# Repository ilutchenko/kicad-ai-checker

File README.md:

# kischk

KiCad schematic checker (early stage).

Current code implements two foundational modules:
- `project loader`: discovers root schematic and resolves hierarchical sheets.
- `schematic parser`: parses `.kicad_sch` S-expressions into an AST.
- `netlist module`: exports/parses KiCad netlist (`kicadsexpr`) from the root schematic.
- `electrical builder`: converts AST into compact LLM-ready electrical model (components/pins/nets).

## Module: Project Loader

Path: `src/kischk/kicad/project.py`

### Purpose
Build a deterministic list of schematic files that belong to a project, starting from a project root directory.

### Main API
- `load_project(project_root: str | Path) -> LoadedProject`

### Input
- `project_root`: filesystem path to KiCad project directory.

### Output
`LoadedProject` dataclass:
- `project_root: Path`
- `project_file: Path | None`
- `root_schematic: Path`
- `schematic_files: tuple[Path, ...]`
- `hierarchy: dict[Path, tuple[Path, ...]]` where key is parent schematic and value is child sheet schematic files.

### How it works
1. Validate `project_root` exists and is a directory.
2. Select `.kicad_pro` file:
- if exactly one exists, use it
- if multiple exist, try `<dir_name>.kicad_pro`
- otherwise raise `ProjectLoaderError`
3. Select root `.kicad_sch`:
- if project file exists, expect same basename (`<project>.kicad_sch`)
- if no project file, infer from available `.kicad_sch` files (single file or `<dir_name>.kicad_sch`)
4. Recursively scan each schematic for hierarchical sheet references:
- locate `(sheet ...)` blocks
- read `(property "Sheetfile" "...")`
- resolve child path relative to parent schematic directory
5. Validate each referenced child exists.
6. Detect cyclic sheet hierarchy and raise `ProjectLoaderError`.

### Error model
Raises `ProjectLoaderError` for:
- missing/invalid project root
- ambiguous or missing root project/schematic
- missing referenced child sheet files
- cyclic hierarchy
- malformed sheet block parentheses

## Module: Schematic Parser (AST)

Path: `src/kischk/kicad/sch_parser.py` and `src/kischk/kicad/sch_model.py`

### Purpose
Parse KiCad S-expression text into a typed AST for further analysis (connectivity, semantic checks, reporting).

### Main API
- `parse_schematic_file(path: str | Path) -> ParsedSchematic`
- `parse_loaded_project(loaded: LoadedProject) -> ParsedProject`
- `parse_project(project_root: str | Path) -> ParsedProject` (loader + parser shortcut)
- `parse_sexpr(text: str, source: Path | None = None) -> SExprList`

### Input
- Single schematic file path (`parse_schematic_file`), or
- `LoadedProject` object from loader (`parse_loaded_project`), or
- project root path (`parse_project`).

### Output
AST dataclasses from `sch_model.py`:
- `SExprAtom(value: str, quoted: bool)`
- `SExprList(items: tuple[SExprNode, ...])`
- `ParsedSchematic(path: Path, root: SExprList)`
- `ParsedProject(schematics: tuple[ParsedSchematic, ...])`

### Parser behavior
- Supports nested lists, symbols, quoted strings, comments (`; ...`), and whitespace.
- Preserves string-vs-symbol distinction via `quoted` flag on atoms.
- Validates schematic top-level node starts with `kicad_sch`.
- Produces precise parse errors with `file:line:column`.

### Error model
Raises `SchematicParseError` for:
- invalid S-expression syntax (unexpected EOF, trailing content, unterminated string, etc.)
- invalid root node (not `kicad_sch`)

## End-to-end data flow

1. `load_project(project_root)` discovers all related schematic files.
2. `parse_loaded_project(loaded)` parses each file into AST.
3. `build_electrical_project(project_root)` exports/parses KiCad netlist and converts AST to compact electrical model.
4. Resulting `ElectricalProject` becomes input for future phases:
- typed schematic model extraction
- connectivity graph construction
- LLM-assisted checks
- report generation

## Module: Electrical Builder (Compact Model)

Path: `src/kischk/kicad/electrical_builder.py` and `src/kischk/kicad/electrical_model.py`

### Purpose
Reduce verbose KiCad AST into electrical information needed for rule checks and LLM prompts.

### Main API
- `build_electrical_project(project_root: str | Path) -> ElectricalProject`
- `build_electrical_from_parsed(loaded: LoadedProject, parsed: ParsedProject, netlist: NetlistData | None = None) -> ElectricalProject`

### Input
- `LoadedProject` + `ParsedProject`, optionally `NetlistData`.
- In `build_electrical_project`, netlist is auto-loaded:
- prefer `<root_schematic_basename>.net` if present
- otherwise export via `kicad-cli sch export netlist --format kicadsexpr`

### Output
`ElectricalProject` dataclass:
- `schematics: tuple[ElectricalSchematic, ...]`
- `nets: tuple[ElectricalNet, ...]`

`ElectricalSchematic`:
- `path`
- `sheet_path` (hierarchical path like `/Root/STM32`)
- `components`

`ElectricalComponent`:
- `reference`, `value`, `lib_id`, `unit`, `uuid`
- `footprint`, `datasheet`, `description`, `lcsc`, `custom_fields` (non-standard user fields only)
- `pins`

`ElectricalPin`:
- `pin_number`, `pin_name`, `direction`
- `is_no_connect`
- `net_id`, `net_name`

`ElectricalNet`:
- `net_id` from KiCad netlist `code` when netlist is available, otherwise geometry fallback (`N0001`, ...)
- optional `net_name`
- `members` (`reference`, `pin_number`)
- attached `labels`
- `is_global`

### Extraction logic
1. Parse library pin definitions from `lib_symbols` to get pin names/directions/relative coordinates.
2. Parse symbol instances (`symbol`) to build components and pin instances.
3. If netlist is available, assign pin `net_id/net_name` from netlist `(net code/name)` by `(ref, pin)`.
4. If netlist provides `pintype`, use it as pin direction in output.
5. If netlist is unavailable, fallback to geometry connectivity (`wire`, `junction`, labels, hierarchy links).

### Error model
Raises `ElectricalBuildError` for internal model consistency problems (for example, missing parsed schematics or unsupported rotations). Netlist export/parse failures are non-fatal in `build_electrical_project` and trigger geometry fallback.

## Module: Netlist

Path: `src/kischk/kicad/netlist.py`

### Purpose
Get reliable net connectivity from KiCad-generated netlist instead of inferring all nets from graphics primitives.

### Main API
- `export_netlist(schematic_file, output_file, fmt=\"kicadsexpr\") -> Path`
- `load_or_export_project_netlist(project_root) -> NetlistData`
- `parse_netlist_file(path) -> NetlistData`

### Output
- `NetlistData(nets=...)`
- `NetlistNet(code, name, net_class, nodes=...)`
- `NetlistNode(ref, pin, pintype, pinfunction)`

## Minimal usage example

```python
from kischk.kicad.project import load_project
from kischk.kicad.sch_parser import parse_loaded_project

loaded = load_project("test_kicad_project")
parsed = parse_loaded_project(loaded)

print(loaded.root_schematic)
print(len(loaded.schematic_files))
print(parsed.schematics[0].root.items[0])  # SExprAtom("kicad_sch", quoted=False)
```

## Current tests

- `tests/test_project_loader.py`
- `tests/test_sch_parser.py`
- `tests/test_netlist.py`
- `tests/test_electrical_builder.py`

Run:

```bash
PYTHONPATH=src python3 -m unittest discover -s tests -v
```

## Evaluation CLI loop

Run evaluation:

```bash
PYTHONPATH=src python3 -m kischk.cli.evaluation test_kicad_project
```

Behavior:
- runs one evaluation iteration, then asks `Run evaluation one more time? [y/N]:`
- `y`/`yes` starts another iteration and creates a new run directory
- default answer is `N` (stop)
- in non-interactive mode (no TTY stdin), it stops after one iteration automatically

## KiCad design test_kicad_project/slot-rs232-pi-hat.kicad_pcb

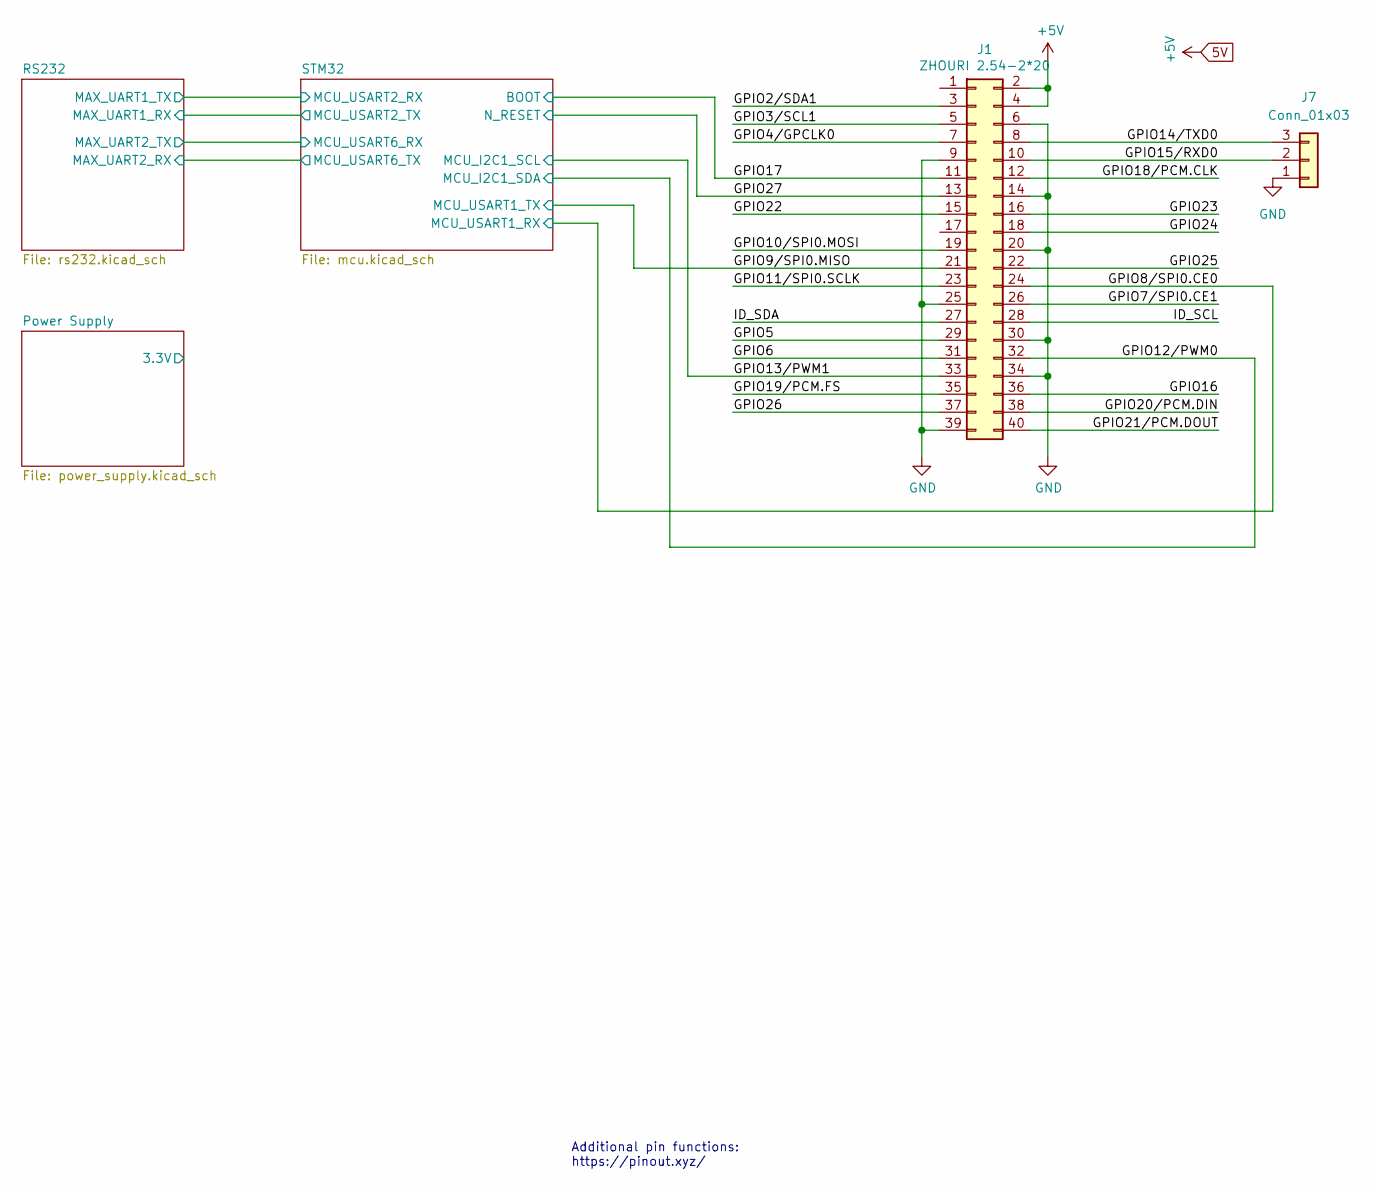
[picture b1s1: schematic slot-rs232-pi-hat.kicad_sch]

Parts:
J1: ZHOURI 2.54-2*20; PinSocket_2x20_P2.54mm_Vertical; LCSC C2977589
J7: Conn_01x03; PinSocket_1x03_P2.54mm_Vertical

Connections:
5V: J1.2, J1.4; also elsewhere on the board
/GPIO2/SDA1: J1.3
/GPIO3/SCL1: J1.5
/GPIO4/GPCLK0: J1.7
/GPIO5: J1.29
/GPIO6: J1.31
/GPIO7/SPI0.CE1: J1.26
/GPIO8/SPI0.CE0: J1.24; also elsewhere on the board
/GPIO9/SPI0.MISO: J1.21; also elsewhere on the board
/GPIO10/SPI0.MOSI: J1.19
/GPIO11/SPI0.SCLK: J1.23
/GPIO12/PWM0: J1.32; also elsewhere on the board
/GPIO13/PWM1: J1.33; also elsewhere on the board
/GPIO14/TXD0: J1.8, J7.3
/GPIO15/RXD0: J1.10, J7.2
/GPIO16: J1.36
/GPIO17: J1.11; also elsewhere on the board
/GPIO18/PCM.CLK: J1.12
/GPIO19/PCM.FS: J1.35
/GPIO20/PCM.DIN: J1.38
/GPIO21/PCM.DOUT: J1.40
/GPIO22: J1.15
/GPIO23: J1.16
/GPIO24: J1.18
/GPIO25: J1.22
/GPIO26: J1.37
/GPIO27: J1.13; also elsewhere on the board
/ID_SCL: J1.28
/ID_SDA: J1.27
GND: J1.6, J1.9, J1.14, J1.20, J1.25, J1.30, J1.34, J1.39, J7.1; also elsewhere on the board

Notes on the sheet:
Additional pin functions: https://pinout.xyz/

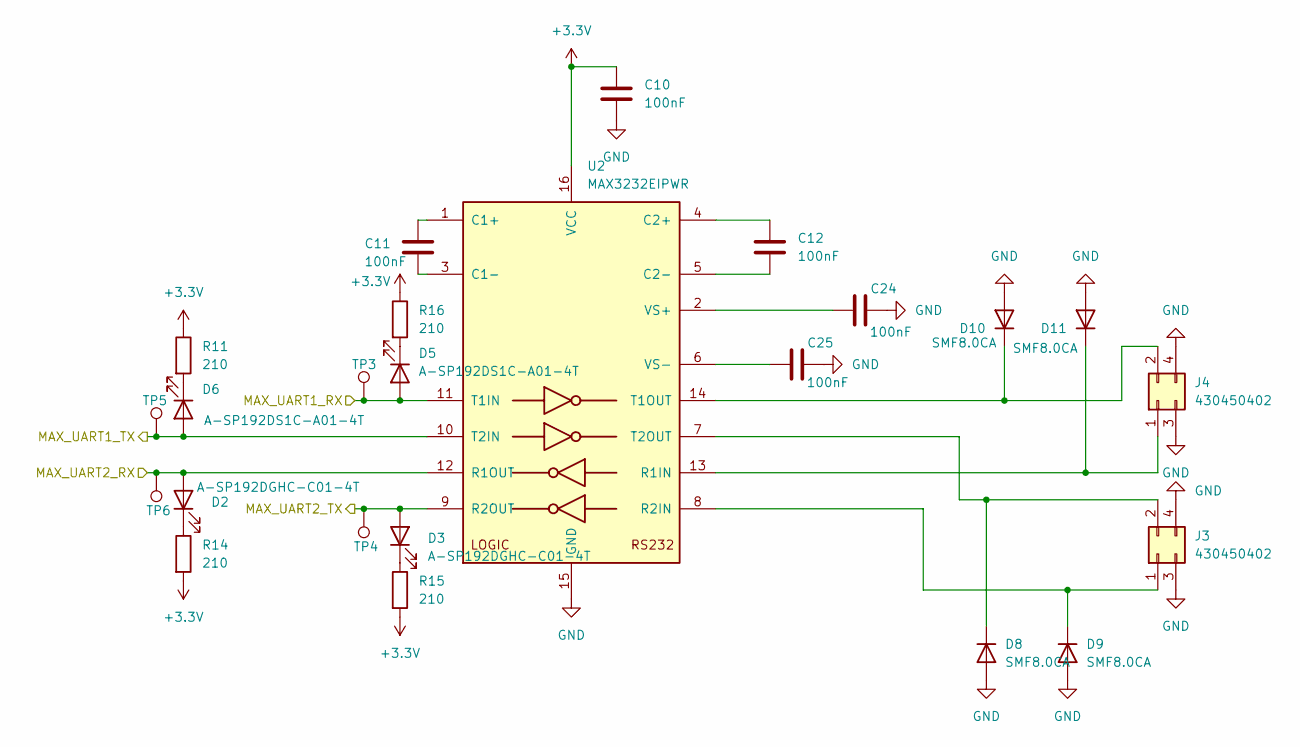
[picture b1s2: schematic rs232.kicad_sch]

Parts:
C10, C11, C12, C24, C25: 100nF; C_0603_1608Metric; LCSC C1590
D2, D3: A-SP192DGHC-C01-4T; LED_0603_1608Metric; LCSC C2286
D5, D6: A-SP192DS1C-A01-4T; LED_0603_1608Metric; LCSC C2286
D8, D9, D10, D11: SMF8.0CA; D_SOD-123F
J3, J4: 430450402; CONN_SD-43045-001_04_MOL; LCSC C587568
R11, R14, R15, R16: 210; R_0603_1608Metric; LCSC C15401
TP3, TP4, TP5, TP6: TestPoint; TestPoint_Pad_D1.5mm
U2: MAX3232EIPWR; TSSOP-16_4.4x5mm_P0.65mm

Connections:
+3.3V: C10.1, R11.1, R14.2, R15.2, R16.1, U2.16 (VCC); also elsewhere on the board
/RS232/MAX_UART1_RX: D5.2 (A), TP3.1, U2.11 (T1IN); also elsewhere on the board
/RS232/MAX_UART1_TX: D6.2 (A), TP5.1, U2.10 (T2IN); also elsewhere on the board
/RS232/MAX_UART2_RX: D2.2 (A), TP6.1, U2.12 (R1OUT); also elsewhere on the board
/RS232/MAX_UART2_TX: D3.2 (A), TP4.1, U2.9 (R2OUT); also elsewhere on the board
GND: C10.2, C24.2, C25.2, D8.2 (A), D9.2 (A), D10.2 (A), D11.2 (A), J3.3, J3.4, J4.3, J4.4, U2.15 (GND); also elsewhere on the board
unnamed: D2.1 (K), R14.1
unnamed: D3.1 (K), R15.1
unnamed: D5.1 (K), R16.2
unnamed: D6.1 (K), R11.2
unnamed: D8.1 (K), J3.2, U2.7 (T2OUT)
unnamed: D9.1 (K), J3.1, U2.8 (R2IN)
unnamed: D10.1 (K), J4.2, U2.14 (T1OUT)
unnamed: D11.1 (K), J4.1, U2.13 (R1IN)
unnamed: C11.1, U2.1 (C1+)
unnamed: C11.2, U2.3 (C1-)
unnamed: C12.1, U2.4 (C2+)
unnamed: C12.2, U2.5 (C2-)
unnamed: C24.1, U2.2 (VS+)
unnamed: C25.1, U2.6 (VS-)

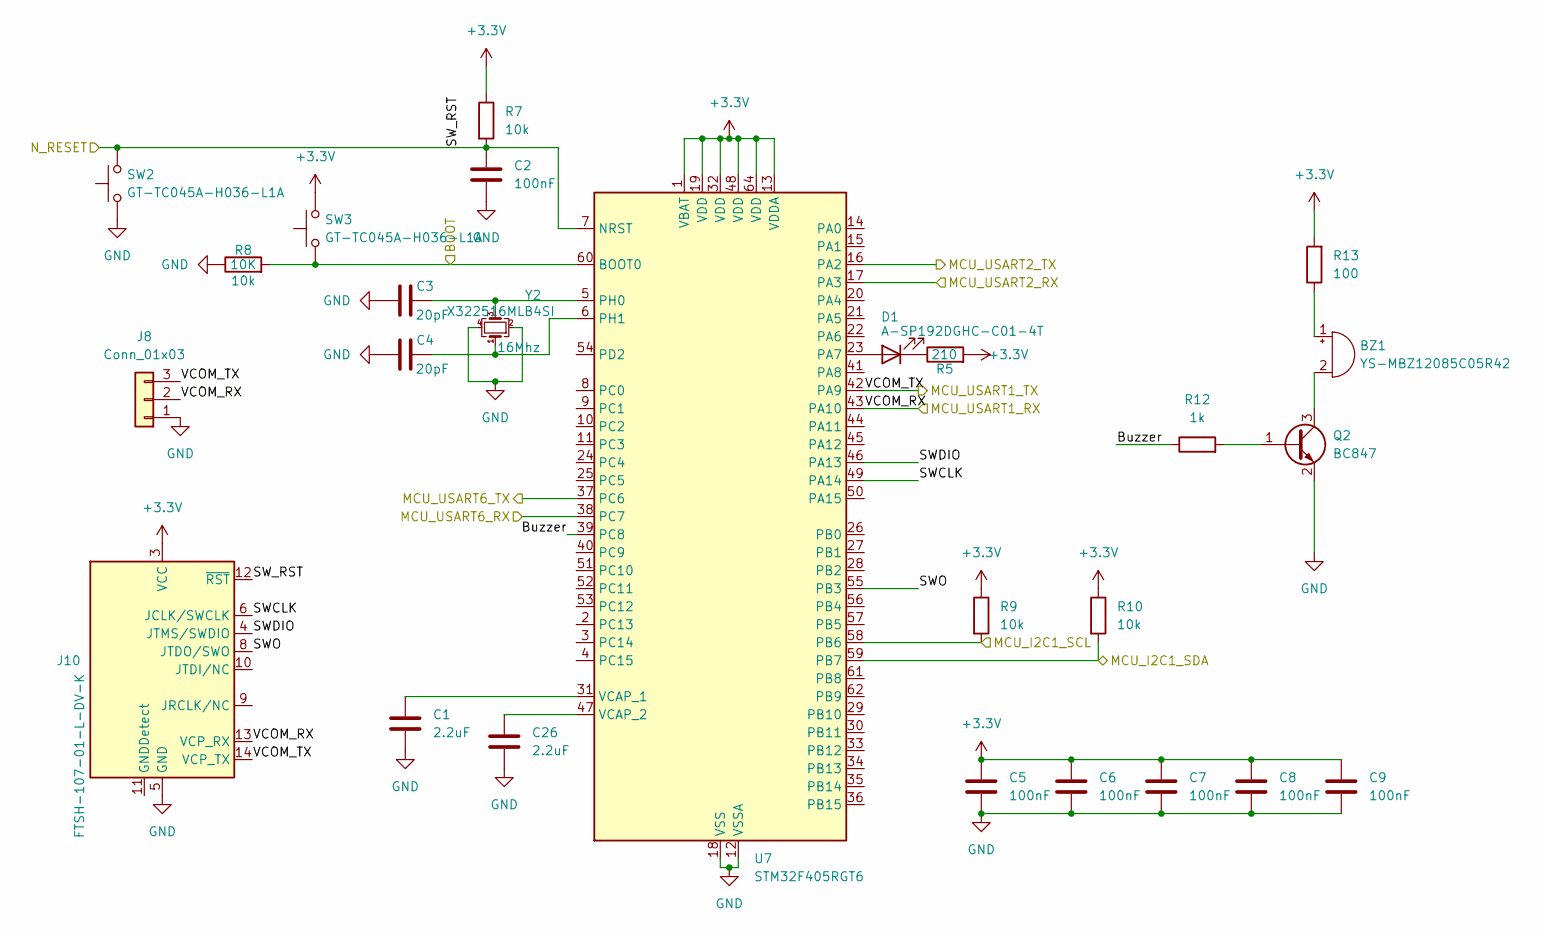
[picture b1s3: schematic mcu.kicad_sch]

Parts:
BZ1: YS-MBZ12085C05R42; Buzzer_TDK_PS1240P02BT_D12.2mm_H6.5mm; LCSC C96256
C1, C26: 2.2uF; C_0603_1608Metric; LCSC C57895
C2, C5, C6, C7, C8, C9: 100nF; C_0603_1608Metric; LCSC C1590
C3, C4: 20pF; C_0603_1608Metric; LCSC C1648
D1: A-SP192DGHC-C01-4T; LED_0603_1608Metric; LCSC C2286
J8: Conn_01x03; PinSocket_1x03_P2.54mm_Vertical
J10: FTSH-107-01-L-DV-K; PinHeader_2x07_P1.27mm_Vertical_SMD
Q2: BC847; SOT-23
R5: 210; R_0603_1608Metric; LCSC C15401
R7, R8, R9, R10: 10k; R_0603_1608Metric; LCSC C15401
R12: 1k; R_0603_1608Metric; LCSC C15401
R13: 100; R_0603_1608Metric; LCSC C15401
SW2, SW3: GT-TC045A-H036-L1A; SW_SPST_EVQP7C
U7: STM32F405RGT6; LQFP-64_10x10mm_P0.5mm
Y2: X322516MLB4SI; Crystal_SMD_3225-4Pin_3.2x2.5mm

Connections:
+3.3V: C5.1, C6.1, C7.1, C8.1, C9.1, J10.3 (VCC), R5.2, R7.1, R9.1, R10.1, R13.2, SW3.2, U7.1 (VBAT), U7.13 (VDDA), U7.19 (VDD), U7.32 (VDD), U7.48 (VDD), U7.64 (VDD); also elsewhere on the board
/GPIO8/SPI0.CE0: J8.2, J10.13 (VCP_RX), U7.43 (PA10); also elsewhere on the board
/GPIO9/SPI0.MISO: J8.3, J10.14 (VCP_TX), U7.42 (PA9); also elsewhere on the board
/GPIO12/PWM0: R10.2, U7.59 (PB7); also elsewhere on the board
/GPIO13/PWM1: R9.2, U7.58 (PB6); also elsewhere on the board
/GPIO17: R8.2, SW3.1, U7.60 (BOOT0); also elsewhere on the board
/GPIO27: C2.1, J10.12 (~RST), R7.2, SW2.2, U7.7 (NRST); also elsewhere on the board
/RS232/MAX_UART1_RX: U7.16 (PA2); also elsewhere on the board
/RS232/MAX_UART1_TX: U7.17 (PA3); also elsewhere on the board
/RS232/MAX_UART2_RX: U7.37 (PC6); also elsewhere on the board
/RS232/MAX_UART2_TX: U7.38 (PC7); also elsewhere on the board
/STM32/Buzzer: R12.1, U7.39 (PC8)
/STM32/SWCLK: J10.6 (JCLK/SWCLK), U7.49 (PA14)
/STM32/SWDIO: J10.4 (JTMS/SWDIO), U7.46 (PA13)
/STM32/SWO: J10.8 (JTDO/SWO), U7.55 (PB3)
GND: C1.2, C2.2, C3.1, C4.1, C5.2, C6.2, C7.2, C8.2, C9.2, C26.2, J8.1, J10.5 (GND), J10.7 (GND), Q2.2 (E), R8.1, SW2.1, U7.12 (VSSA), U7.18 (VSS), U7.63 (VSS), Y2.2, Y2.4; also elsewhere on the board
unnamed 39: BZ1.2 (-), Q2.3 (C); also elsewhere on the board
unnamed 40: BZ1.1 (+), R13.1; also elsewhere on the board
unnamed: D1.2 (A), U7.23 (PA7)
unnamed: D1.1 (K), R5.1
unnamed: Q2.1 (B), R12.2
unnamed: C3.2, U7.5 (PH0), Y2.3
unnamed: C4.2, U7.6 (PH1), Y2.1
unnamed: C1.1, U7.31 (VCAP_1)
unnamed: C26.1, U7.47 (VCAP_2)

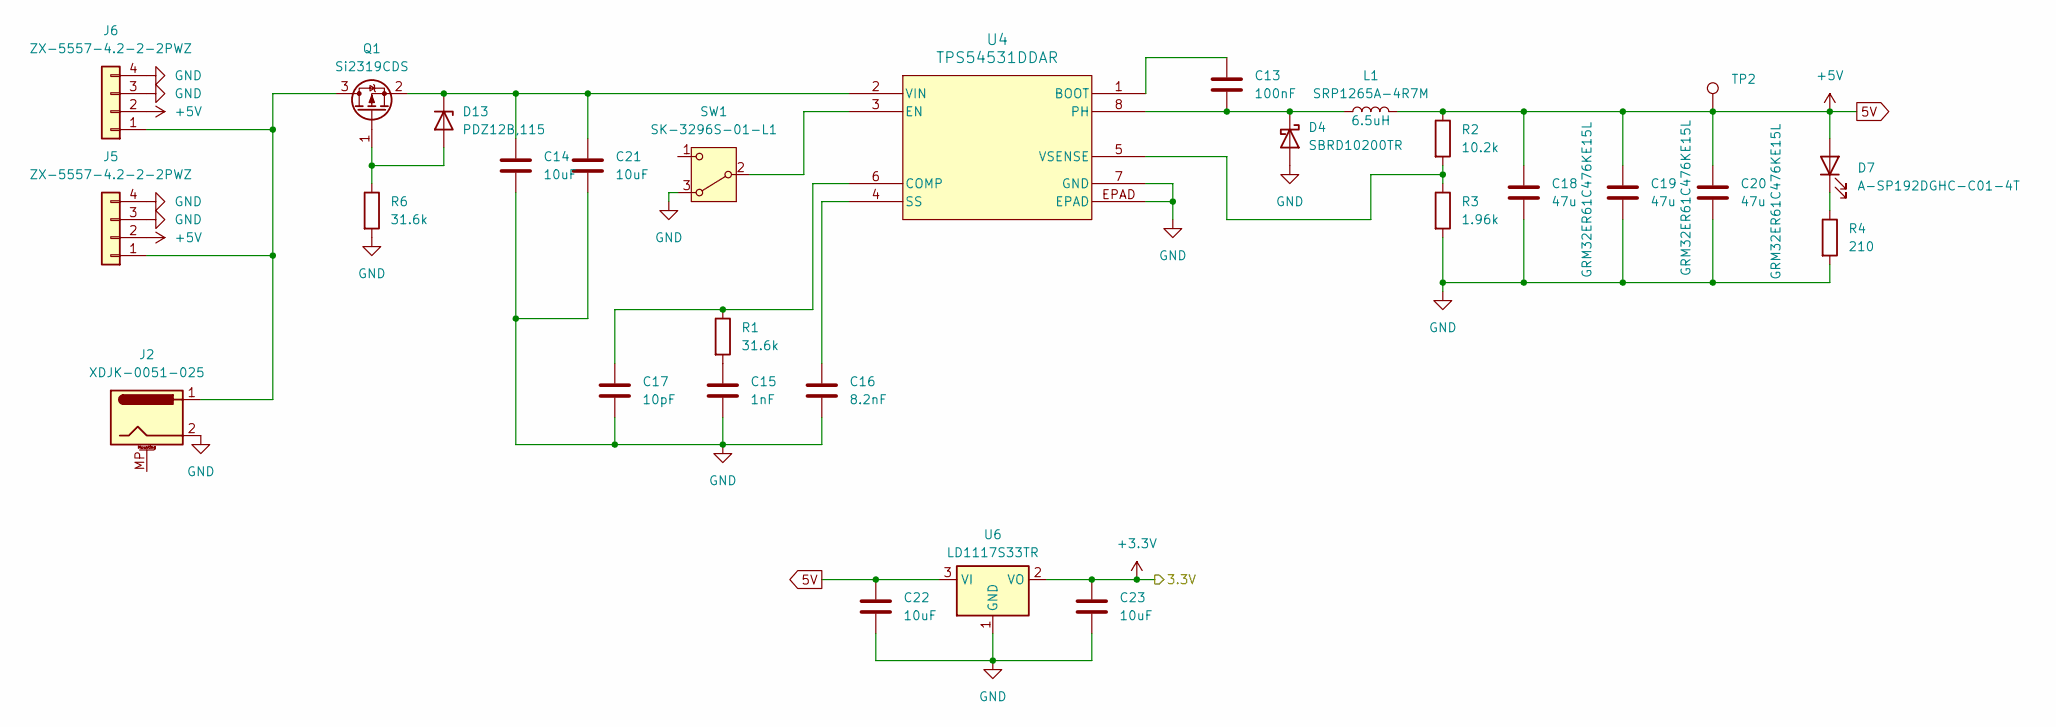
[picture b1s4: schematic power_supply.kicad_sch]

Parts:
C13: 100nF; C_0603_1608Metric; LCSC C1590
C14, C21, C22, C23: 10uF; C_1210_3225Metric; LCSC C39232
C15: 1nF; C_0603_1608Metric; LCSC C1588
C16: 8.2nF; C_0603_1608Metric; LCSC C113812
C17: 10pF; C_0603_1608Metric; LCSC C1634
C18, C19, C20: 47u; C_1210_3225Metric; LCSC C77101
D4: SBRD10200TR; TO-252-2; LCSC C784374
D7: A-SP192DGHC-C01-4T; LED_0603_1608Metric; LCSC C2286
D13: PDZ12B,115; D_SOD-323
J2: XDJK-0051-025; BarrelJack_GCT_DCJ200-10-A_Horizontal; LCSC C7498153
J5, J6: ZX-5557-4.2-2-2PWZ; CONN04_1724480004_MOL; LCSC C7541564
L1: SRP1265A-4R7M; SRR1208-6R5ML; LCSC C780205
Q1: Si2319CDS; SOT-23
R1, R6: 31.6k; R_0603_1608Metric; LCSC C25967
R2: 10.2k; R_0603_1608Metric; LCSC C22772
R3: 1.96k; R_0603_1608Metric; LCSC C100838
R4: 210; R_0603_1608Metric; LCSC C22772
SW1: SK-3296S-01-L1; SW_SPDT_PCM12
TP2: TestPoint; TestPoint_Pad_D1.5mm
U4: TPS54531DDAR; DDA8_3P1X2P4_TEX; LCSC C50605
U6: LD1117S33TR; SOT-223-3_TabPin2; LCSC C86781

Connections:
5V: C18.1, C19.1, C20.1, C22.1, D7.2 (A), J5.2, J6.2, L1.2, R2.1, TP2.1, U6.3 (VI); also elsewhere on the board
+3.3V: C23.1, U6.2 (VO); also elsewhere on the board
GND: C14.2, C15.2, C16.2, C17.2, C18.2, C19.2, C20.2, C21.2, C22.2, C23.2, D4.2 (A), J2.2, J5.3, J5.4, J6.3, J6.4, R3.2, R4.2, R6.2, SW1.3 (A), U4.7 (GND), U4.EPAD, U6.1 (GND); also elsewhere on the board
unnamed: C15.1, R1.2
unnamed: C13.2, D4.1 (K), L1.1, U4.8 (PH)
unnamed: D7.1 (K), R4.1
unnamed: D13.2 (A), Q1.1 (G), R6.1
unnamed: C14.1, C21.1, D13.1 (K), Q1.2 (S), U4.2 (VIN)
unnamed: J2.1, J5.1, J6.1, Q1.3 (D)
unnamed: SW1.2 (B), U4.3 (EN)
unnamed: C13.1, U4.1 (BOOT)
unnamed: C17.1, R1.1, U4.6 (COMP)
unnamed: C16.1, U4.4 (SS)
unnamed: R2.2, R3.1, U4.5 (VSENSE)

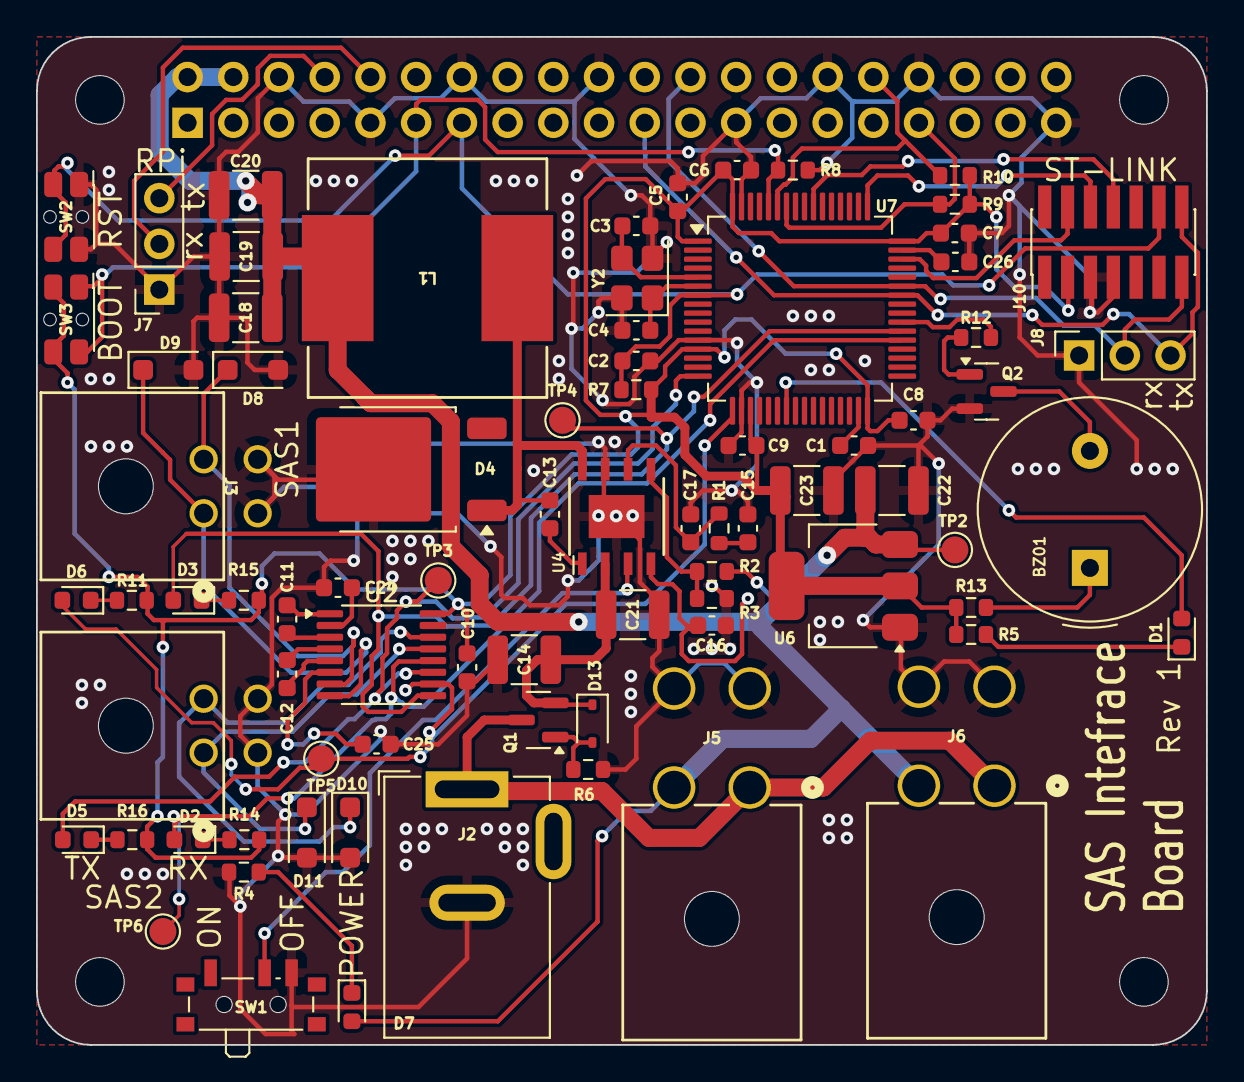
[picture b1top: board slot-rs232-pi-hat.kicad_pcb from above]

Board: 2 copper layers, 65.0 x 56.0 mm, 84 parts (1 on the bottom side), 53 nets.

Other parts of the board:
BZ01: YS-MBZ12085C05R42; Buzzer_TDK_PS1240P02BT_D12.2mm_H6.5mm
MH1, MH2, MH3, MH4: MountingHole_2.7mm_M2.5

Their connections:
unnamed 39: BZ01.1 (+); also elsewhere on the board
unnamed 40: BZ01.2 (-); also elsewhere on the board

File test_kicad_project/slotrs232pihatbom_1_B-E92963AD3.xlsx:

BOM File: |  | slotrs232pihatbom_1 |  |  |  |  |  |  | Order ID： | B-E92963AD3 |  |  |  | Quote Time: | 2025/07/22 21:37:03
Purchase Quantity： |  | 5 pcs |  |  |  |  |  |  | BOM Total ($)： | 71.56
Inquiry |  |  |  |  |  |  |  |  | HQNextPCB-Quotation
S/N | Designator* | Quantity* | Manufacturer Part Number* | Manufacturer | Package /Footprint | Description | Procurement Type | Customer Note | Quote MPN | Quote Brand | Package /Footprint | Plan Qty | Overage Amount | Quote Qty | Unit Price($) | Subtotal($) | Lead Time | Question from HQ NextPCB | Customer Reply
1 | R3 | 1 | AC0603FR-071K96L |  | R_0603_1608Metric | 1.96k |  |  |  |  |  | 5 | 5 | 10 | 0 | 0 |  | please provide the complete model | Added
2 | C16 | 1 | CC0603KRX7R9BB822 |  | C_0603_1608Metric | 8.2nF |  |  |  |  |  | 5 | 5 | 10 | 0 | 0 |  | please provide the complete model | Added
3 | Y2 | 1 | X322516MLB4SI |  | Crystal_SMD_3225-4Pin_3.2x2.5mm | X322516MLB4SI |  |  | X322516MLB4SI | YXC | SMD3225_4P | 5 | 5 | 10 | 0.04602 | 0.46 | In Stock
4 | Q1 | 1 | Si2319CDS |  | SOT-23 | Si2319CDS |  |  | SI2319CDS | TECH PUBLIC | SOT-23 | 5 | 15 | 20 | 0.07381 | 1.48 | In Stock
5 | R10,R11,R12,R13,R14,R15,R16,R5,R7,R8,R9 | 11 | RC0603FR-0710KL |  | R_0603_1608Metric | 10k |  |  |  |  |  | 55 | 5 | 60 | 0 | 0 |  | please provide the complete model | Added
6 | U7 | 1 | STM32F405RGT6 |  | LQFP-64_10x10mm_P0.5mm | STM32F405RGT6 |  |  | STM32F405RGT6 | ST | LQFP64_10X10MM | 5 | 0 | 5 | 2.58339 | 12.92 | In Stock
7 | C15 | 1 | CC0603KRX7R9BB102 |  | C_0603_1608Metric | 1nF |  |  |  |  |  | 5 | 5 | 10 | 0 | 0 |  | please provide the complete model | Added
8 | C10,C11,C12,C13,C2,C24,C25,C5,C6,C7,C8,C9 | 12 | TCC0603X7R104K101CT |  | C_0603_1608Metric | 100nF |  |  |  |  |  | 60 | 40 | 100 | 0 | 0 |  | please provide the complete model | Added
9 | C17 | 1 | CL10C100JB81PNC |  | C_0603_1608Metric | 10pF |  |  |  |  |  | 5 | 5 | 10 | 0 | 0 |  | please provide the complete model | Added
10 | C3,C4 | 2 | AC0603JRNPO9BN200 |  | C_0603_1608Metric | 20pF |  |  |  |  |  | 10 | 5 | 15 | 0 | 0 |  | please provide the complete model | Added
11 | D13 | 1 | PDZ12B,115 |  | D_SOD-323 | PDZ12B,115 |  |  | PDZ12B,115 | Nexperia | SOD-323 | 5 | 30 | 35 | 0.02744 | 0.96 | In Stock
12 | D10,D11,D8,D9 | 4 | SMF8.0CA |  | D_SOD-123F | SMF8.0CA |  |  | SMF8.0CA | JXND | SOD-123FL | 20 | 30 | 50 | 0.00946 | 0.47 | In Stock
13 | R2,R4 | 2 | AC0603FR-0710K2L |  | R_0603_1608Metric | 10.2k |  |  |  |  |  | 10 | 5 | 15 | 0 | 0 |  | please provide the complete model | Added
14 | D1,D2,D3,D5,D6,D7 | 6 | A-SP192DGHC-C01-4T |  | LED_0603_1608Metric | A-SP192DGHC-C01-4T |  |  | A-SP192DGHC-C01-4T | Amicc | 0603 | 30 | 40 | 70 | 0.0215 | 1.51 | In Stock
15 | R1,R6 | 2 | RT0603BRD0731K6L |  | R_0603_1608Metric | 31.6k |  |  |  |  |  | 10 | 5 | 15 | 0 | 0 |  | please provide the complete model | Added
16 | J1 | 1 | ZHOURI 2.54-2*20 |  | PinSocket_2x20_P2.54mm_Vertical | ZHOURI 2.54-2*20 |  |  | 2.54-2*20 | ZHOURI(洲日) | CONN_51.05X5.08MM_TM | 5 | 3 | 8 | 0.21048 | 1.68 | 4-7 Days
17 | SW1 | 1 | SK-3296S-01-L1 |  | SW_SPDT_PCM12 | SK-3296S-01-L1 |  |  | SK-3296S-01-L1 | XKB | SW7_6.6X2.7MM_SM | 5 | 5 | 10 | 0.03367 | 0.34 | In Stock
18 | C14,C21,C22,C23 | 4 | 1210B106K500CT |  | C_1210_3225Metric | 10uF |  |  |  |  |  | 20 | 40 | 60 | 0 | 0 |  | please provide the complete model | Added
19 | U2 | 1 | MAX3232EIPWR |  | TSSOP-16_4.4x5mm_P0.65mm | MAX3232EIPWR |  |  | MAX3232EIPWR | TI | TSSOP16_5X4.4MM | 5 | 2 | 7 | 0.2076 | 1.45 | In Stock
20 | U4 | 1 | TPS54531DDAR |  | SO-8_3.9x4.9mm_P1.27mm | TPS54531DDAR |  |  | TPS54531DDAR | TI | SOIC8_150MIL_EP | 5 | 2 | 7 | 0.28848 | 2.02 | In Stock
21 | SW2,SW3 | 2 | GT-TC045A-H036-L1A |  | SW_SPST_EVQP7C | GT-TC045A-H036-L1A |  |  | GT-TC045A-H036-L1A | G-Switch(品赞) | SMD | 10 | 3 | 13 | 0.14455 | 1.88 | 4-7 Days
22 | J10 | 1 | FTSH-107-01-L-DV-K |  | PinHeader_2x07_P1.27mm_Vertical_SMD | FTSH-107-01-L-DV-K |  |  | FTSH-107-01-L-DV-K | SAMTEC | SMD,P=1.27mm | 5 | 1 | 6 | 3.24842 | 19.49 | 4-7 Days
23 | C1,C26 | 2 | CL10A225KB8NNNC |  | C_0603_1608Metric | 2.2uF |  |  |  |  |  | 10 | 5 | 15 | 0 | 0 |  | please provide the complete model | Added
24 | J3,J4 | 2 | 430450402 |  | CONN_SD-43045-001_04_MOL | 430450402 |  |  | 430450402 | Molex(莫仕) | 插件,P=3mm | 10 | 1 | 11 | 1.07943 | 11.87 | 3-5 Days
25 | J2 | 1 | XDJK-0051-025 |  | BarrelJack_GCT_DCJ200-10-A_Horizontal | XDJK-0051-025 |  |  | XDJK-0051-025 | LX(连欣科技) | 插件 | 5 | 3 | 8 | 0.08583 | 0.69 | 4-7 Days
26 | J5,J6 | 2 | ZX-5557-4.2-2-2PWZ |  | CONN04_1724480004_MOL | ZX-5557-4.2-2-2PWZ |  |  | ZX-5557-4.2-2-2PWZ | Megastar(兆星) | 弯插,P=4.2mm | 10 | 3 | 13 | 0.12344 | 1.6 | 4-7 Days
27 | C18,C19,C20 | 3 | TMK325ABJ476MM-P |  | C_1210_3225Metric | 47u |  |  |  |  |  | 15 | 5 | 20 | 0 | 0 |  | please provide the complete model | Added
28 | L1 | 1 | SRP1265A-4R7M |  | SRR1208-6R5ML | SRP1265A-4R7M |  |  | SRP1265A-4R7M | Bourns | 1265 | 5 | 2 | 7 | 0.65354 | 4.57 | In Stock
29 | D4 | 1 | SBRD10200TR |  | TO-252-2 | SBRD10200TR |  |  | SBRD10200 | SMC Diode Solutions | TO-252-3, DPAK (2 Leads + Tab), SC-63 | 5 | 1 | 6 | 1.04258 | 6.26 | 7-18 Days | please confirm if this MPN is OK to use? | Yes, it’s ok
30 | Q2 | 1 | BC847 |  | SOT-23 | BC847 |  |  | BC847 | SK | SOT-23 | 5 | 15 | 20 | 0.00927 | 0.19 | In Stock
31 | U6 | 1 | LD1117S33TR |  | SOT-223-3_TabPin2 | LD1117S33TR |  |  | LD1117S33TR | ST | SOT-223-3 | 5 | 3 | 8 | 0.12904 | 1.03 | In Stock
32 | BZ1 | 1 | YS-MBZ12085C05R42 |  | Buzzer_12x9.5RM7.6 | YS-MBZ12085C05R42 |  |  | YS-MBZ12085C05R42 | FENGMING(锋鸣电子) | 插件,D=12mm | 5 | 5 | 10 | 0.06932 | 0.69 | 4-7 Days

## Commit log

2026-02-22 docs: add kikad file format description
2026-02-22 test: add test kicad project
2026-03-03 docs: add AGENTS.md
2026-03-03 Initialize project loader with hierarchy resolution and tests
2026-03-03 Add KiCad schematic AST parser wired to project loader
2026-03-03 agents: add note about .gitignore file updating
2026-03-03 Document loader/parser flow and ignore local artifacts
2026-03-04 Refine electrical model fields and remove duplicated component metadata
2026-03-04 Use KiCad netlist export for authoritative pin-to-net mapping
2026-04-17 agents: add some notes about readme
2026-04-17 src: add main entry file
2026-04-18 prompts: add initial detector prompt
2026-04-18 src: check: add detector call
2026-04-18 src: check: add detector model argument
2026-04-18 src: add initial evaluation script
2026-04-18 test_project: update with new mistakes
2026-04-18 src: add results evaluation script
2026-04-18 prompts: update known mistakes. split leds reverse polarity to each led separately
2026-04-18 evaluation: calculate detected and total number of mistakes
2026-04-18 prompts: add preprocessing editor prompt
2026-04-18 prompts: add detector prompt editor
2026-04-18 prompts: detector: change to GPT version
2026-04-18 prompts: small change in detector editor
2026-04-18 prompts: preprocessing editor: change to GPT version
2026-04-18 src: add detector prompt editor
2026-04-18 prompts: result_checker: change to GPT version
2026-04-18 src: add preprocessing editor
2026-04-18 prompts: detector editor: change to GPT version
2026-04-18 src: evaluation: change mistakes calculation
2026-04-18 src: collect token consumption statistics
2026-04-18 src: evaluation: ryn in loop
2026-04-18 gitignore: add .codex
